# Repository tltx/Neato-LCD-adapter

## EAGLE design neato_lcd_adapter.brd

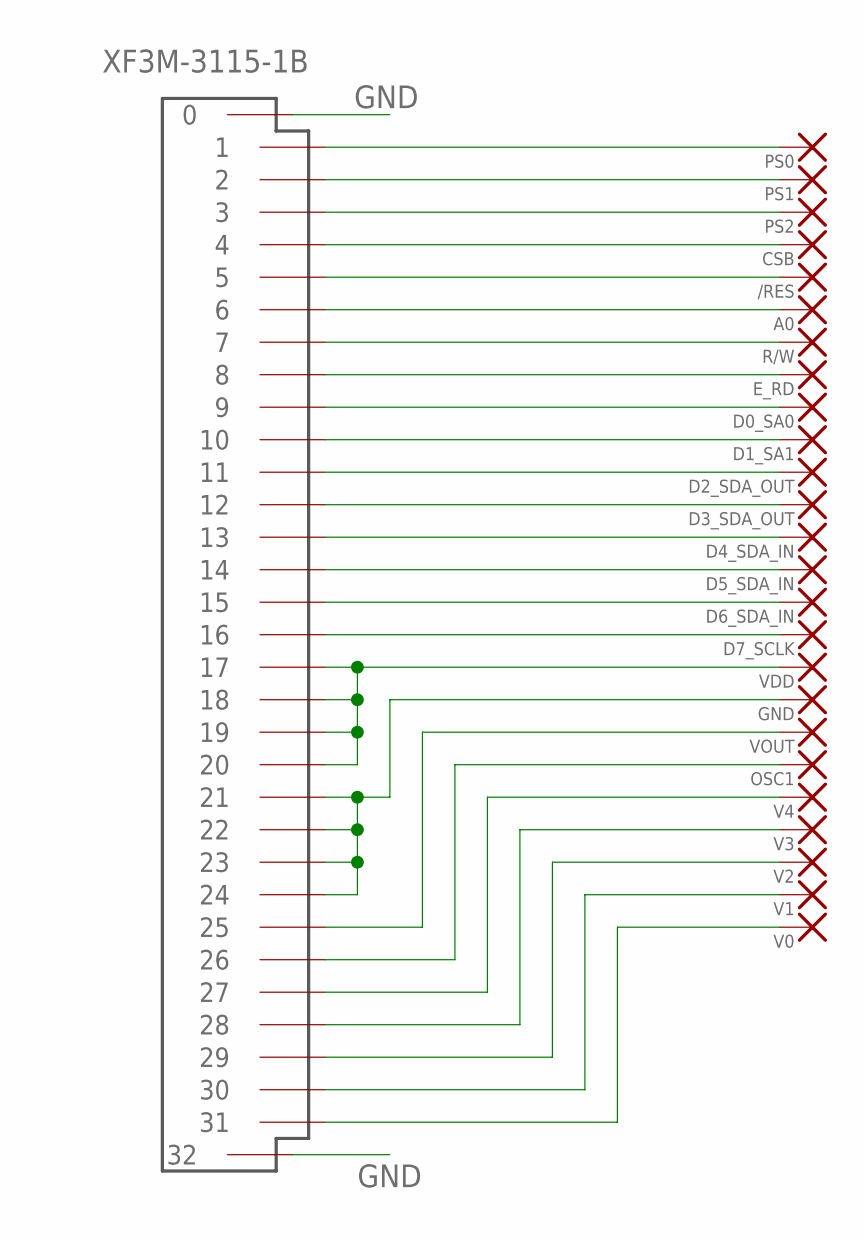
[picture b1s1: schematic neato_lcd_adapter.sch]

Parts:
/RES: SMD2; SMD_PAD
A0: SMD2; SMD_PAD
CSB: SMD2; SMD_PAD
D0_SA0, D1_SA1, D2_SDA_OUT, D3_SDA_OUT, D4_SDA_IN, D5_SDA_IN, D6_SDA_IN, D7_SCLK: SMD2; SMD_PAD
E_RD: SMD2; SMD_PAD
GND: SMD2; SMD_PAD
LCD: XF3M-3115-1B; FPC-31P-0.5MM
OSC1: SMD2; SMD_PAD
PS0, PS1, PS2: SMD2; SMD_PAD
R/W: SMD2; SMD_PAD
V0, V1, V2, V3, V4: SMD2; SMD_PAD
VDD: SMD2; SMD_PAD
VOUT: SMD2; SMD_PAD

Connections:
GND: LCD.P$1 (0), LCD.P$2 (32)
unnamed: LCD.P$3 (1), PS0.1
unnamed: LCD.P$4 (2), PS1.1
unnamed: LCD.P$5 (3), PS2.1
unnamed: CSB.1, LCD.P$6 (4)
unnamed: /RES.1, LCD.P$7 (5)
unnamed: A0.1, LCD.P$8 (6)
unnamed: LCD.P$9 (7), R/W.1
unnamed: E_RD.1, LCD.P$10 (8)
unnamed: D0_SA0.1, LCD.P$11 (9)
unnamed: D1_SA1.1, LCD.P$12 (10)
unnamed: D2_SDA_OUT.1, LCD.P$13 (11)
unnamed: D3_SDA_OUT.1, LCD.P$14 (12)
unnamed: D4_SDA_IN.1, LCD.P$15 (13)
unnamed: D5_SDA_IN.1, LCD.P$16 (14)
unnamed: D6_SDA_IN.1, LCD.P$17 (15)
unnamed: D7_SCLK.1, LCD.P$18 (16)
unnamed: LCD.P$19 (17), LCD.P$20 (18), LCD.P$21 (19), LCD.P$22 (20), VDD.1
unnamed: GND.1, LCD.P$23 (21), LCD.P$24 (22), LCD.P$25 (23), LCD.P$26 (24)
unnamed: LCD.P$27 (25), VOUT.1
unnamed: LCD.P$28 (26), OSC1.1
unnamed: LCD.P$29 (27), V4.1
unnamed: LCD.P$30 (28), V3.1
unnamed: LCD.P$31 (29), V2.1
unnamed: LCD.P$32 (30), V1.1
unnamed: LCD.P$33 (31), V0.1

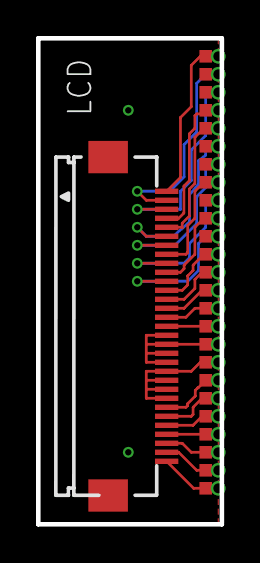
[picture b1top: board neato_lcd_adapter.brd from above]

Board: 2 copper layers, 10.2 x 27.0 mm, 26 parts (0 on the bottom side), 26 nets.
